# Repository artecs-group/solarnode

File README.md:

# Solar Node

This is a kikad project for a pcb of a IoT node that can meassure Solar Irradiation
and send it truogh a wifi conection to a cloud service.

The node ins based on an ESP32, which provides the microcontroller and the wifi
radio. The pcb adds a power supply system and a solar irradiance meassurement
circuit.

The power supply system is composed of a Lipo battery, a battery charger, a 6W
solar pannel and a set of regulators: one for the esp, and two for external
devices that can be swithced on or off from the ESP firmware.

The solar irradiance meassurement circuit is composed of a transimpedance
amplifier and a small mono-chrystalline fotovoltaic cell, that is kept in short
circuit by the transimpedance amplifier, which transforms the current generated
by the cell into a voltage that can be read using one of the ADC channels of the
ESP32. Bellow you can see an image of a complete node build from this pcb.

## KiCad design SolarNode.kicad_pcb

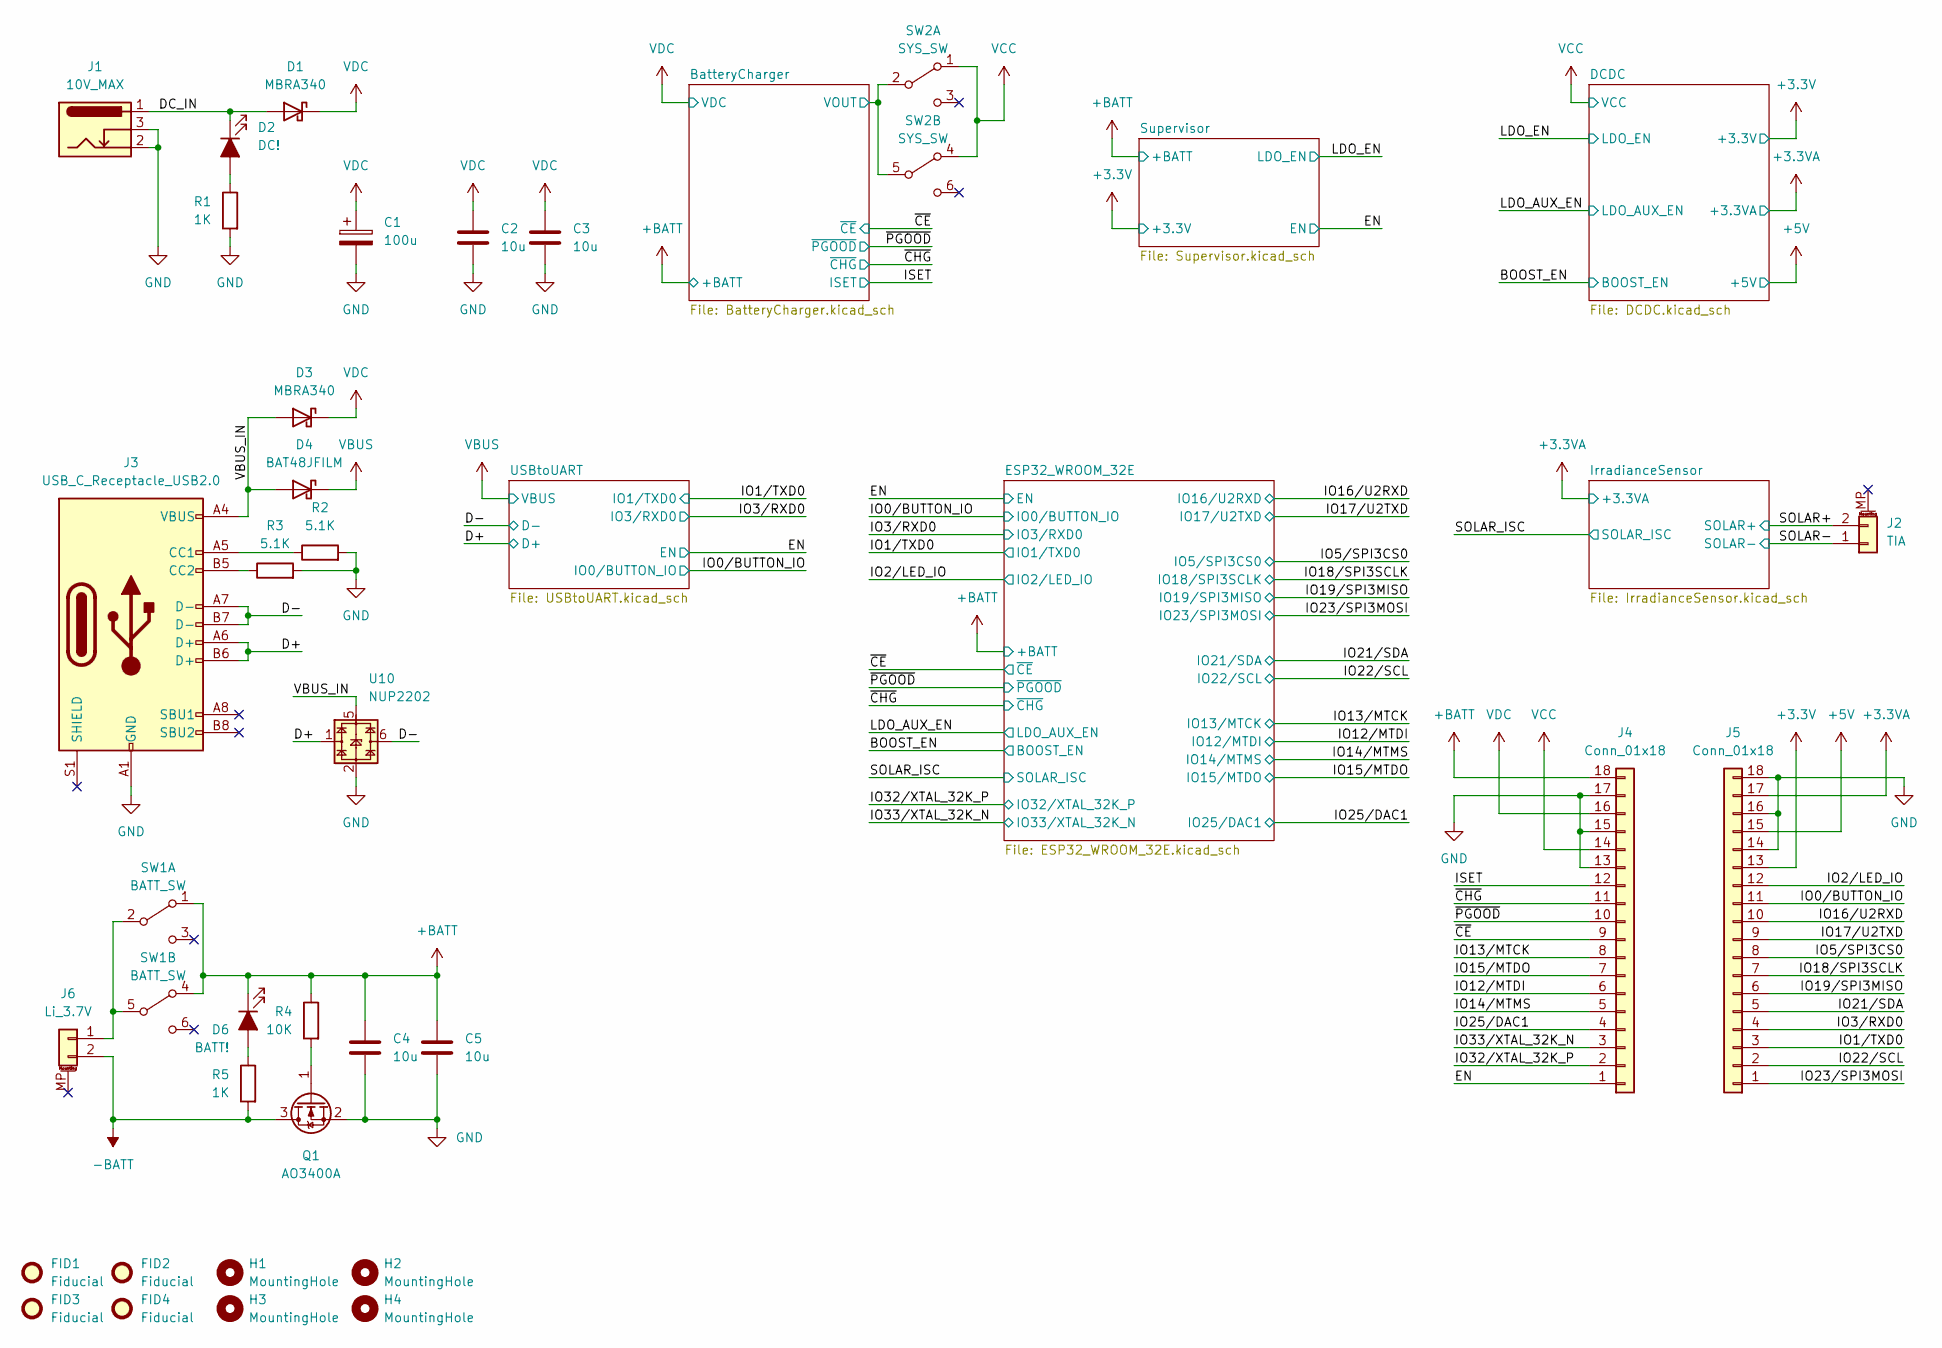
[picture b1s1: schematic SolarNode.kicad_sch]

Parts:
C1: 100u; CP_Radial_D6.3mm_P2.50mm; MPN 16YXF100MEFCT16.3X11
C2, C3, C4, C5: 10u; C_0603_1608Metric; MPN CC0603MRX5R7BB106
D1, D3: MBRA340; D_SMA; MPN MBRA340
D2: DC!; LED_0603_1608Metric; MPN 150060SS75000
D4: BAT48JFILM; D_SOD-323; MPN BAT48JFILM
D6: BATT!; LED_0603_1608Metric; MPN 150060SS75000
FID1, FID2, FID3, FID4: Fiducial; Fiducial_1mm_Mask3mm
H1, H2, H3, H4: MountingHole; MountingHole_2.2mm_M2
J1: 10V_MAX; BarrelJack_CLIFF_FC681465S_SMT_Horizontal; MPN FC681465S
J2: TIA; JST_PH_S2B-PH-SM4-TB_1x02-1MP_P2.00mm_Horizontal; MPN S2B-PH-SM4-TB(LF)(SN)
J3: USB_C_Receptacle_USB2.0; GCT_USB4110-GF-A_REVB; MPN USB4110-GF-A
J4, J5: Conn_01x18; PinHeader_1x18_P2.54mm_Vertical; MPN PH1-18-UA
J6: Li_3.7V; JST_PH_S2B-PH-SM4-TB_1x02-1MP_P2.00mm_Horizontal; MPN S2B-PH-SM4-TB(LF)(SN)
Q1: AO3400A; SOT-23; MPN AO3400A
R1, R5: 1K; R_0603_1608Metric_0.65; MPN RC0603FR-071KL
R2, R3: 5.1K; R_0603_1608Metric_0.65; MPN RC0603FR-075K1L
R4: 10K; R_0603_1608Metric_0.65; MPN RC0603FR-0710KL
SW1: BATT_SW; SW_DPDT_CK_JS202011JCQN; MPN JS202011JCQN
SW2: SYS_SW; SW_DPDT_CK_JS202011JCQN; MPN JS202011JCQN
U10: NUP2202; SOT-363_SC-70-6; MPN NUP2202W1T2G

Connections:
+3.3VA: J5.17; also elsewhere on the board
+3V3: J5.13; also elsewhere on the board
+5V: J5.15; also elsewhere on the board
+BATT: C4.1, C5.1, D6.1 (K), J4.18, R4.1, SW1.1 (A), SW1.4 (A); also elsewhere on the board
-BATT: J6.2, Q1.3 (D), R5.2
/BatteryCharger/VOUT: SW2.2 (B), SW2.5 (B); also elsewhere on the board
/D+: J3.A6 (D+), J3.B6 (D+), U10.1; also elsewhere on the board
/D-: J3.A7 (D-), J3.B7 (D-), U10.6; also elsewhere on the board
/DC_IN: D1.2 (A), D2.1 (K), J1.1
/EN: J4.1; also elsewhere on the board
/IO0/BUTTON_IO: J5.11; also elsewhere on the board
/IO1/TXD0: J5.3; also elsewhere on the board
/IO2/LED_IO: J5.12; also elsewhere on the board
/IO3/RXD0: J5.4; also elsewhere on the board
/IO5/SPI3CS0: J5.8; also elsewhere on the board
/IO12/MTDI: J4.6; also elsewhere on the board
/IO13/MTCK: J4.8; also elsewhere on the board
/IO14/MTMS: J4.5; also elsewhere on the board
/IO15/MTDO: J4.7; also elsewhere on the board
/IO16/U2RXD: J5.10; also elsewhere on the board
/IO17/U2TXD: J5.9; also elsewhere on the board
/IO18/SPI3SCLK: J5.7; also elsewhere on the board
/IO19/SPI3MISO: J5.6; also elsewhere on the board
/IO21/SDA: J5.5; also elsewhere on the board
/IO22/SCL: J5.2; also elsewhere on the board
/IO23/SPI3MOSI: J5.1; also elsewhere on the board
/IO25/DAC1: J4.4; also elsewhere on the board
/IO32/XTAL_32K_P: J4.2; also elsewhere on the board
/IO33/XTAL_32K_N: J4.3; also elsewhere on the board
/ISET: J4.12; also elsewhere on the board
/SOLAR+: J2.2; also elsewhere on the board
/SOLAR-: J2.1; also elsewhere on the board
/VBUS_IN: D3.2 (A), D4.2 (A), J3.A4 (VBUS), J3.A9 (VBUS), J3.B4 (VBUS), J3.B9 (VBUS), U10.5
/~CE: J4.9; also elsewhere on the board
/~CHG: J4.11; also elsewhere on the board
/~PGOOD: J4.10; also elsewhere on the board
GND: C1.2, C2.2, C3.2, C4.2, C5.2, J1.2, J1.3, J3.A1 (GND), J3.A12 (GND), J3.B1 (GND), J3.B12 (GND), J4.13, J4.15, J4.17, J5.14, J5.16, J5.18, Q1.2 (S), R1.2, R2.2, R3.2, U10.2; also elsewhere on the board
unnamed: D2.2 (A), R1.1
unnamed: D6.2 (A), R5.1
unnamed: J3.A5 (CC1), R2.1
unnamed: J3.B5 (CC2), R3.1
unnamed: J6.1, SW1.2 (B), SW1.5 (B)
unnamed: Q1.1 (G), R4.2
VBUS: D4.1 (K); also elsewhere on the board
VCC: J4.14, SW2.1 (A), SW2.4 (A); also elsewhere on the board
VDC: C1.1, C2.1, C3.1, D1.1 (K), D3.1 (K), J4.16; also elsewhere on the board

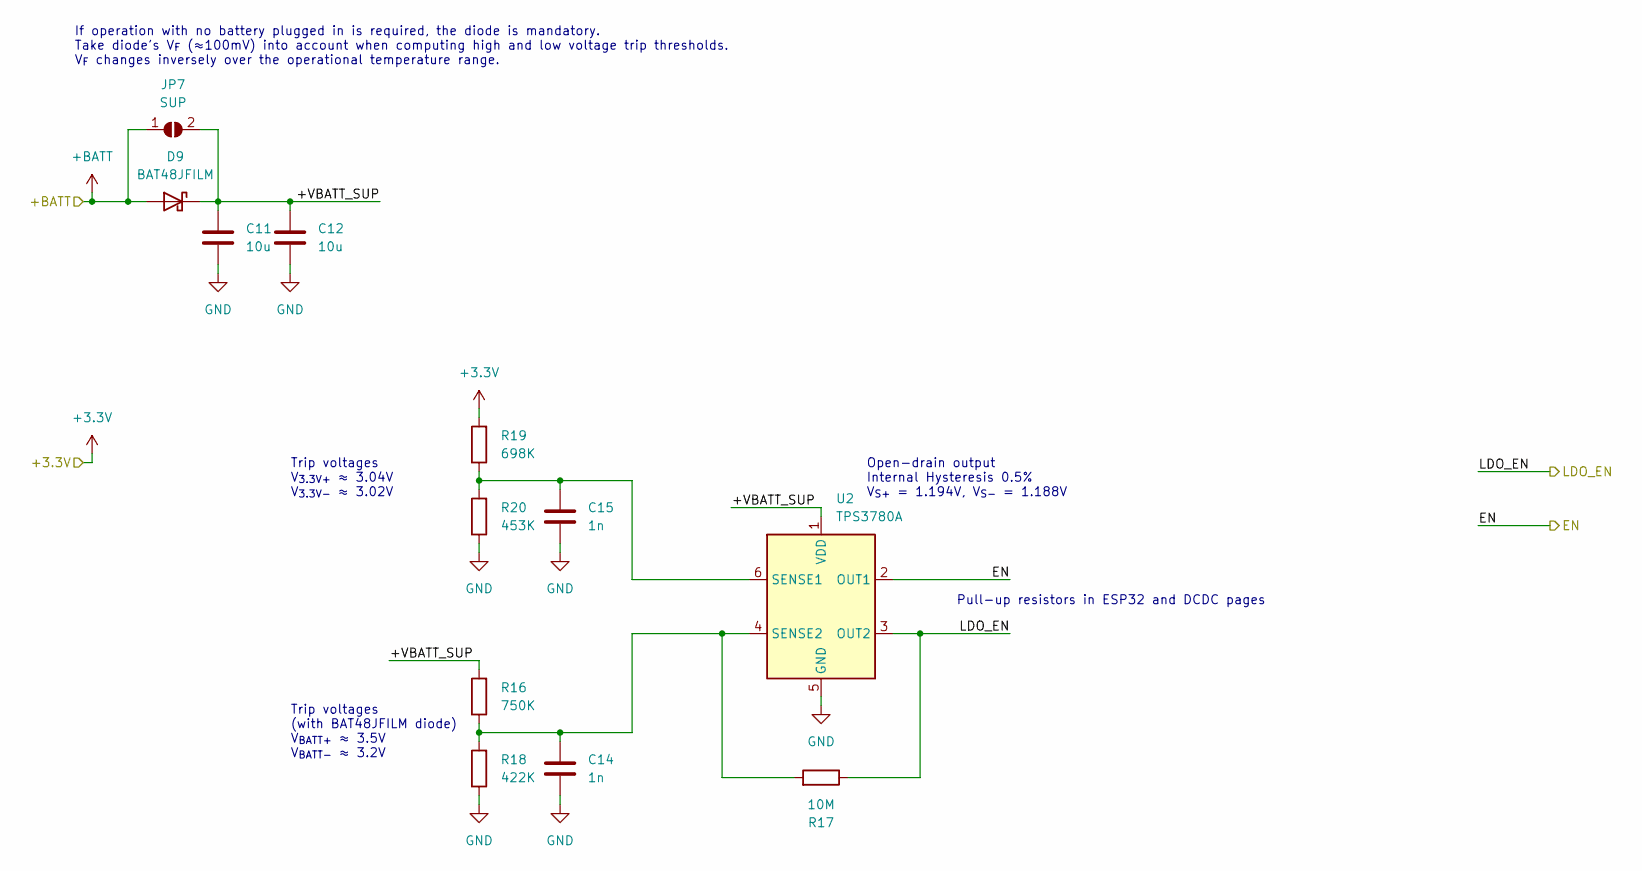
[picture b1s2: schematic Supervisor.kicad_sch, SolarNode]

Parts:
C11, C12: 10u; C_0603_1608Metric; MPN CC0603MRX5R7BB106
C14, C15: 1n; C_0603_1608Metric; MPN CC0603KRX7R9BB102
D9: BAT48JFILM; D_SOD-323; MPN BAT48JFILM
JP7: SUP; SolderJumper-2_P1.3mm_Open_RoundedPad1.0x1.5mm
R16: 750K; R_0603_1608Metric_0.65; MPN RC0603FR-07750KL
R17: 10M; R_0603_1608Metric_0.65; MPN RC0603FR-0710ML
R18: 422K; R_0603_1608Metric_0.65; MPN RC0603FR-07422KL
R19: 698K; R_0603_1608Metric_0.65; MPN RC0603FR-07698KL
R20: 453K; R_0603_1608Metric_0.65; MPN RC0603FR-07453KL
U2: TPS3780A; SOT-23-6; MPN TPS3780ADBVT

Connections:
+3V3: R19.2; also elsewhere on the board
+BATT: D9.2 (A), JP7.1 (A); also elsewhere on the board
/EN: U2.2 (OUT1); also elsewhere on the board
/LDO_EN: R17.1, U2.3 (OUT2); also elsewhere on the board
/Supervisor/+VBATT_SUP: C11.1, C12.1, D9.1 (K), JP7.2 (B), R16.2, U2.1 (VDD)
GND: C11.2, C12.2, C14.2, C15.2, R18.1, R20.1, U2.5 (GND); also elsewhere on the board
unnamed: C14.1, R16.1, R17.2, R18.2, U2.4 (SENSE2)
unnamed: C15.1, R19.1, R20.2, U2.6 (SENSE1)

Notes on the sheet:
Trip voltages V_{3.3V+} ≈ 3.04V V_{3.3V-} ≈ 3.02V
Pull-up resistors in ESP32 and DCDC pages
Trip voltages (with BAT48JFILM diode) V_{BATT+} ≈ 3.5V V_{BATT-} ≈ 3.2V
If operation with no battery plugged in is required, the diode is mandatory. Take diode's V_{F} (≈100mV) into account when computing high and low voltage trip thresholds. V_{F} changes inversely over the operational temperature range.
Open-drain output Internal Hysteresis 0.5% V_{S+} = 1.194V, V_{S-} = 1.188V

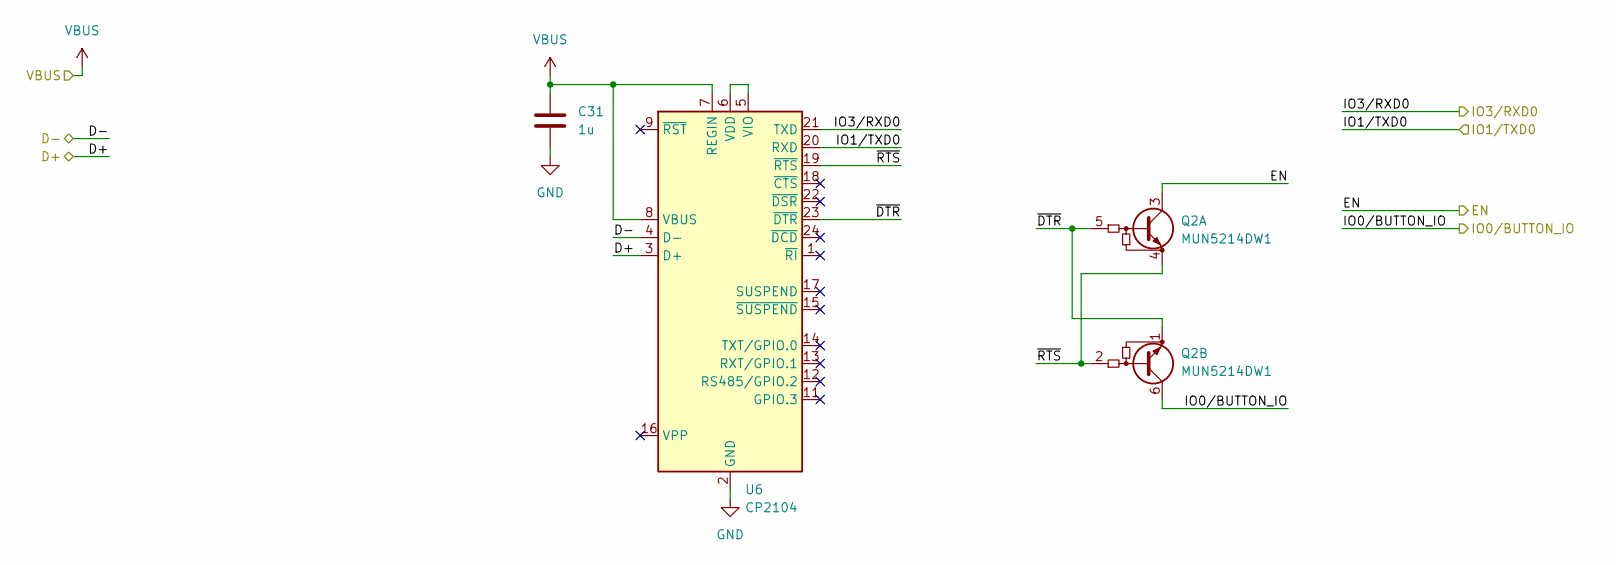
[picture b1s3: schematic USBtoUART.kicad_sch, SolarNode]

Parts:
C31: 1u; C_0603_1608Metric; MPN CC0603KRX7R8BB105
Q2: MUN5214DW1; SOT-363_SC-70-6; MPN MUN5214DW1T1G
U6: CP2104; QFN-24-1EP_4x4mm_P0.5mm_EP2.6x2.6mm; MPN CP2104-F03-GM

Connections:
/D+: U6.3 (D+); also elsewhere on the board
/D-: U6.4 (D-); also elsewhere on the board
/EN: Q2.3 (C1); also elsewhere on the board
/IO0/BUTTON_IO: Q2.6 (C2); also elsewhere on the board
/IO1/TXD0: U6.20 (RXD); also elsewhere on the board
/IO3/RXD0: U6.21 (TXD); also elsewhere on the board
/USBtoUART/~DTR: Q2.1 (E2), Q2.5 (B1), U6.23 (~DTR)
/USBtoUART/~RTS: Q2.2 (B2), Q2.4 (E1), U6.19 (~RTS)
GND: C31.2, U6.2 (GND), U6.25 (GND); also elsewhere on the board
unnamed: U6.5 (VIO), U6.6 (VDD)
VBUS: C31.1, U6.7 (REGIN), U6.8 (VBUS); also elsewhere on the board

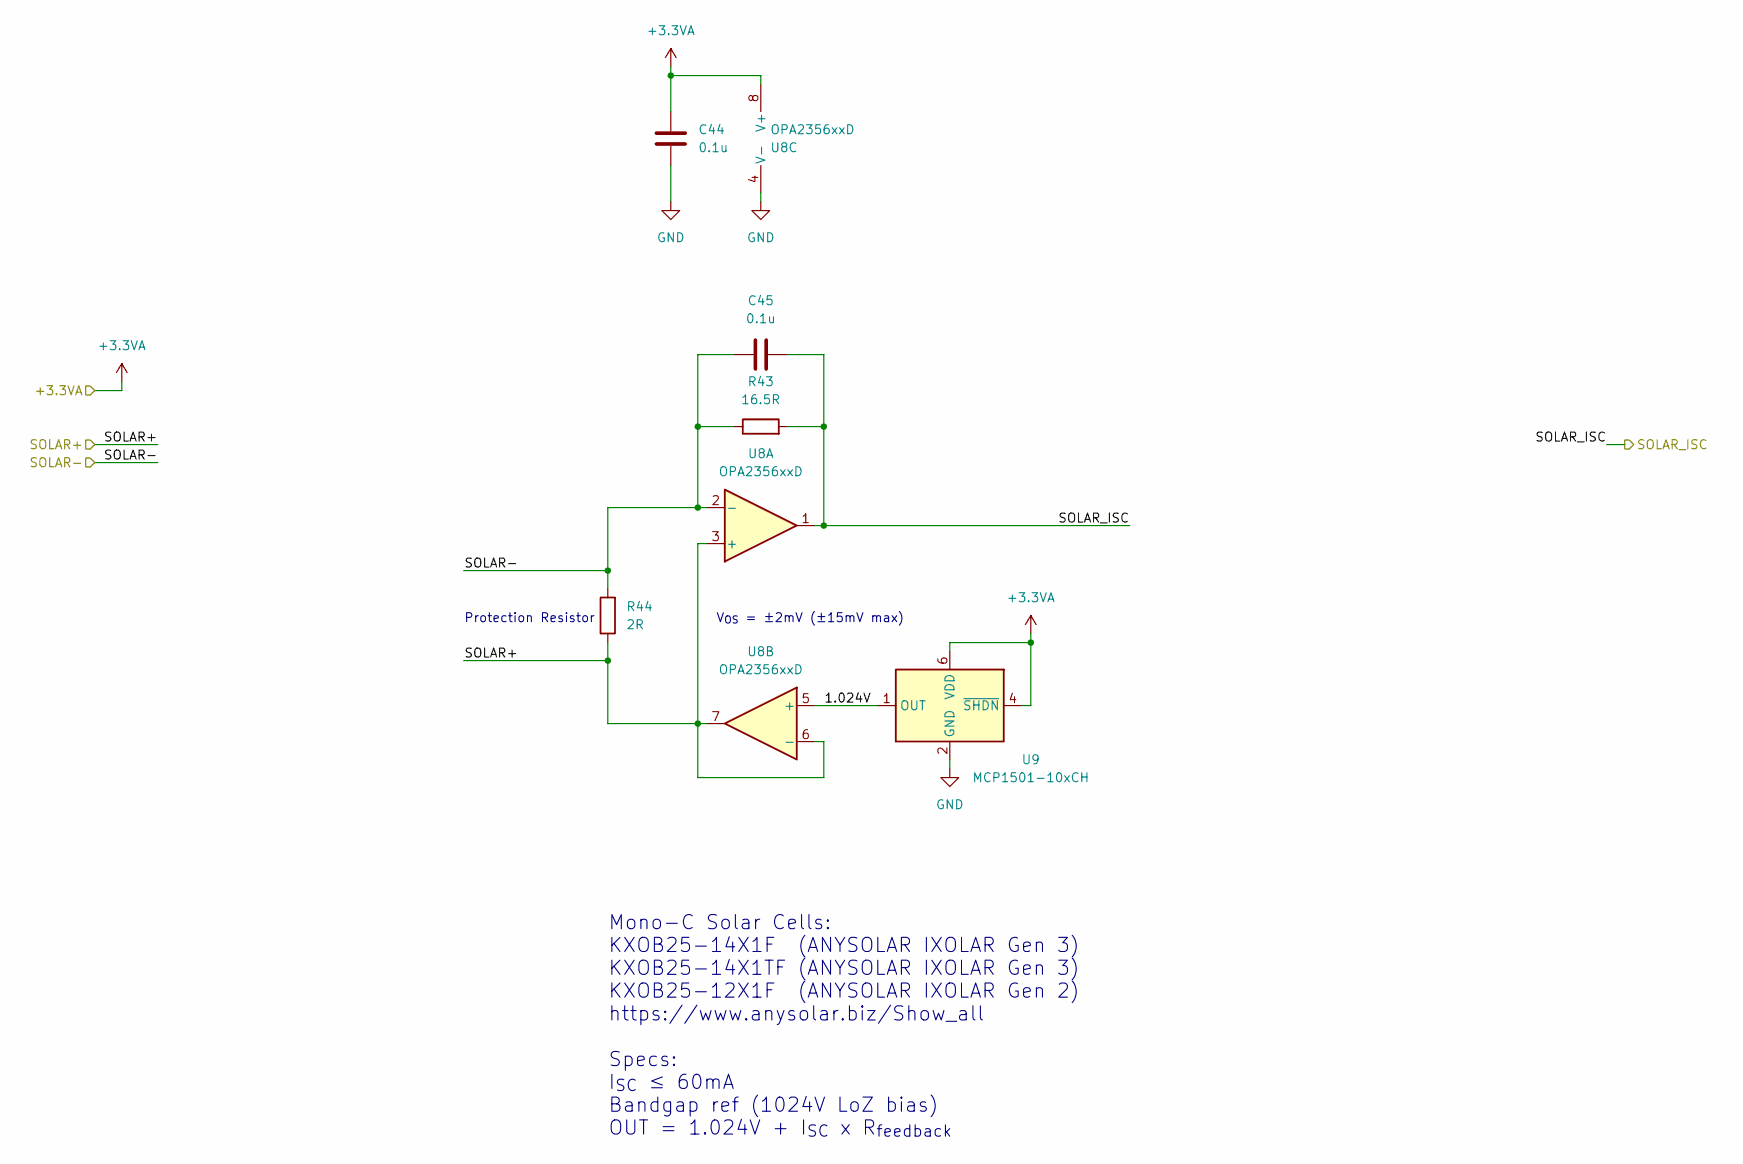
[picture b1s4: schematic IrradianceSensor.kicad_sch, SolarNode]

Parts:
C44, C45: 0.1u; C_0603_1608Metric; MPN CC0603KRX7R9BB104
R43: 16.5R; R_0603_1608Metric_0.65; MPN RC0603FR-0716R5L
R44: 2R; R_0603_1608Metric_0.65; MPN RC0603FR-072RL
U8: OPA2356xxD; MSOP-8_3x3mm_P0.65mm; MPN OPA2356AIDGKR
U9: MCP1501-10xCH; SOT-23-6; MPN MCP1501T-10E/CHY

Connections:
+3.3VA: C44.1, U8.8 (V+), U9.4 (~SHDN), U9.6 (VDD); also elsewhere on the board
/IrradianceSensor/1.024V: U8.5 (+), U9.1 (OUT)
/SOLAR+: R44.1, U8.3 (+), U8.6 (-), U8.7; also elsewhere on the board
/SOLAR-: C45.1, R43.1, R44.2, U8.2 (-); also elsewhere on the board
/SOLAR_ISC: C45.2, R43.2, U8.1; also elsewhere on the board
GND: C44.2, U8.4 (V-), U9.2 (GND), U9.3 (GND), U9.5 (GND); also elsewhere on the board

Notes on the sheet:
Mono-C Solar Cells: KXOB25-14X1F (ANYSOLAR IXOLAR Gen 3) KXOB25-14X1TF (ANYSOLAR IXOLAR Gen 3) KXOB25-12X1F (ANYSOLAR IXOLAR Gen 2) https://www.anysolar.biz/Show_all Specs: I_{SC} ≤ 60mA Bandgap ref (1024V LoZ bias) OUT = 1.024V + I_{SC} x R_{feedback}
V_{OS} = ±2mV (±15mV max)
Protection Resistor

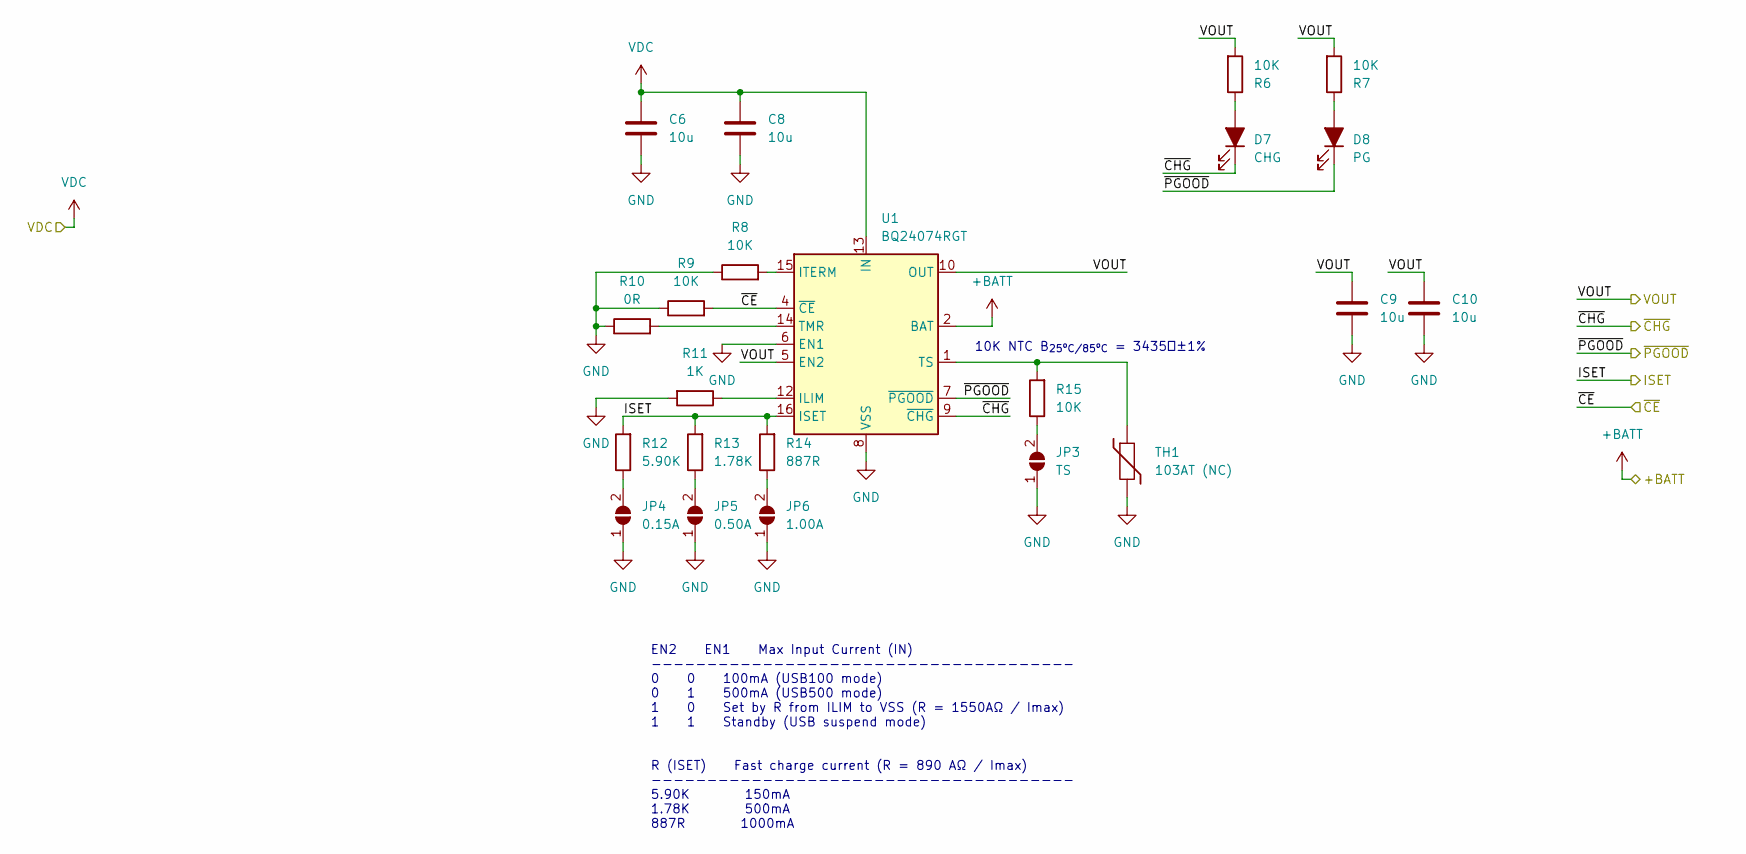
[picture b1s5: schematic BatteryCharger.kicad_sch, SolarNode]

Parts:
C6, C8, C9, C10: 10u; C_0603_1608Metric; MPN CC0603MRX5R7BB106
D7: CHG; LED_0603_1608Metric; MPN 150060SS75000
D8: PG; LED_0603_1608Metric; MPN 150060VS75000
JP3: TS; SolderJumper-2_P1.3mm_Open_RoundedPad1.0x1.5mm
JP4: 0.15A; SolderJumper-2_P1.3mm_Open_RoundedPad1.0x1.5mm
JP5: 0.50A; SolderJumper-2_P1.3mm_Open_RoundedPad1.0x1.5mm
JP6: 1.00A; SolderJumper-2_P1.3mm_Open_RoundedPad1.0x1.5mm
R6, R7, R8, R9, R15: 10K; R_0603_1608Metric_0.65; MPN RC0603FR-0710KL
R10: 0R; R_0603_1608Metric_0.65; MPN RC0603FR-070RL
R11: 1K; R_0603_1608Metric_0.65; MPN RC0603FR-071KL
R12: 5.90K; R_0603_1608Metric_0.65; MPN RC0603FR-075K9L
R13: 1.78K; R_0603_1608Metric_0.65; MPN RC0603FR-071K78L
R14: 887R; R_0603_1608Metric_0.65; MPN RC0603FR-07887RL
TH1: 103AT (NC); C_Disc_D5.0mm_W2.5mm_P2.50mm; MPN 103AT-2
U1: BQ24074RGT; VQFN-16-1EP_3x3mm_P0.5mm_EP1.6x1.6mm_ThermalVias; MPN BQ24074RGT

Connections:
+BATT: U1.2 (BAT), U1.3 (BAT); also elsewhere on the board
/BatteryCharger/VOUT: C9.1, C10.1, R6.2, R7.2, U1.5 (EN2), U1.10 (OUT), U1.11 (OUT); also elsewhere on the board
/ISET: R12.2, R13.2, R14.2, U1.16 (ISET); also elsewhere on the board
/~CE: R9.2, U1.4 (~CE); also elsewhere on the board
/~CHG: D7.1 (K), U1.9 (~CHG); also elsewhere on the board
/~PGOOD: D8.1 (K), U1.7 (~PGOOD); also elsewhere on the board
GND: C6.2, C8.2, C9.2, C10.2, JP3.1 (A), JP4.1 (A), JP5.1 (A), JP6.1 (A), R8.1, R9.1, R10.1, R11.2, TH1.2, U1.6 (EN1), U1.8 (VSS), U1.17 (VSS); also elsewhere on the board
unnamed: D7.2 (A), R6.1
unnamed: D8.2 (A), R7.1
unnamed: JP3.2 (B), R15.1
unnamed: JP4.2 (B), R12.1
unnamed: JP5.2 (B), R13.1
unnamed: JP6.2 (B), R14.1
unnamed: R8.2, U1.15 (ITERM)
unnamed: R10.2, U1.14 (TMR)
unnamed: R11.1, U1.12 (ILIM)
unnamed: R15.2, TH1.1, U1.1 (TS)
VDC: C6.1, C8.1, U1.13 (IN); also elsewhere on the board

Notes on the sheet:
EN2 EN1 Max Input Current (IN) -------------------------------------- 0 0 100mA (USB100 mode) 0 1 500mA (USB500 mode) 1 0 Set by R from ILIM to VSS (R = 1550AΩ / Imax) 1 1 Standby (USB suspend mode) R (ISET) Fast charge current (R = 890 AΩ / Imax) -------------------------------------- 5.90K 150mA 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
10K NTC B_{25ºC/85ºC} = 3435Ｋ±1%

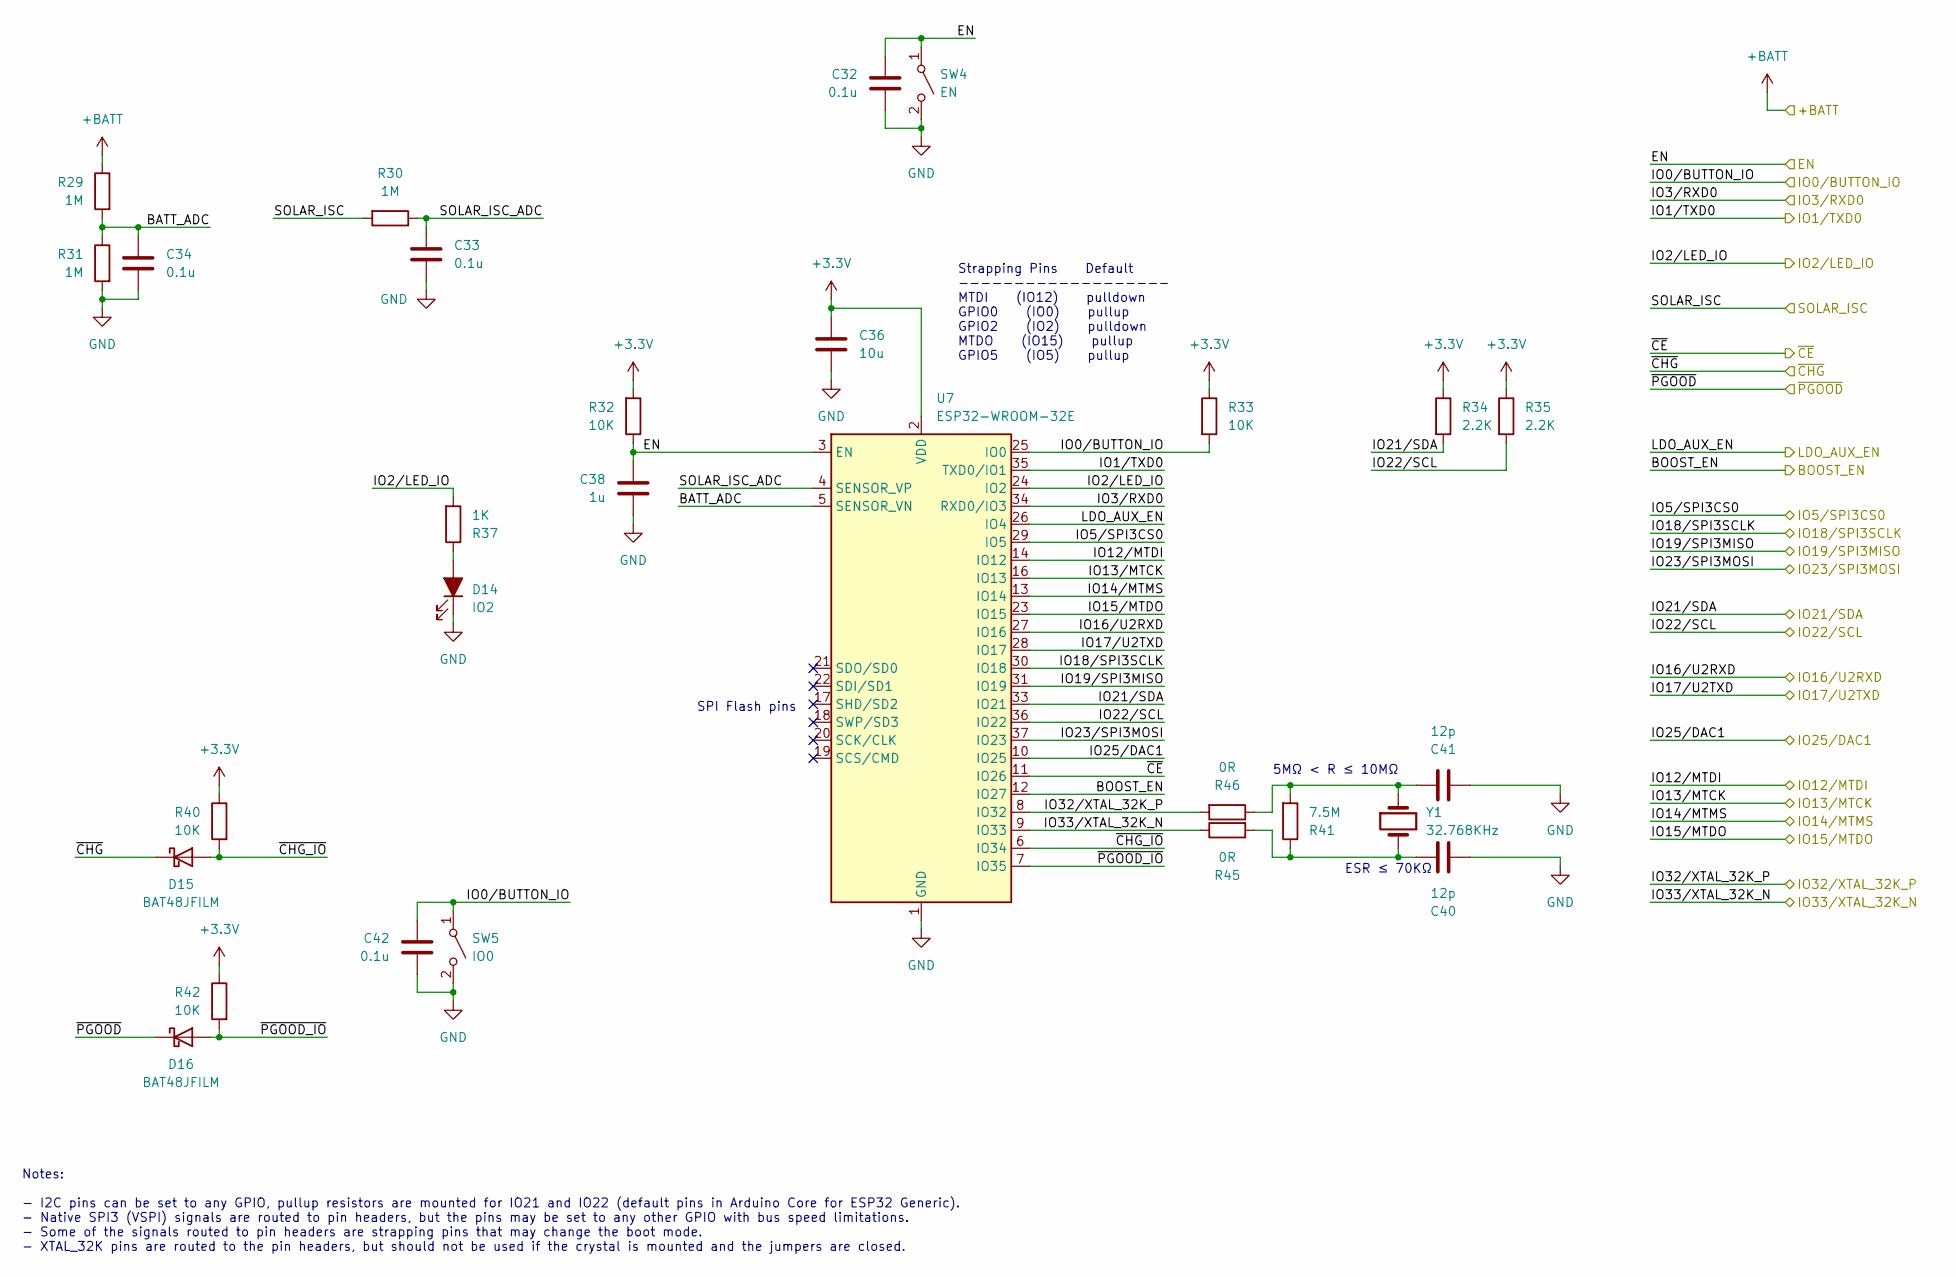
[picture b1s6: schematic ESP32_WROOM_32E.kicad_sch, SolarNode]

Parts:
C32, C33, C34, C42: 0.1u; C_0603_1608Metric; MPN CC0603KRX7R9BB104
C36: 10u; C_0603_1608Metric; MPN CC0603MRX5R7BB106
C38: 1u; C_0603_1608Metric; MPN CC0603KRX7R8BB105
C40, C41: 12p; C_0603_1608Metric; MPN CC0603KRNPO9BN120
D14: IO2; LED_0603_1608Metric; MPN 150060VS75000
D15, D16: BAT48JFILM; D_SOD-323; MPN BAT48JFILM
R29, R30, R31: 1M; R_0603_1608Metric_0.65; MPN RC0603FR-071ML
R32, R33, R40, R42: 10K; R_0603_1608Metric_0.65; MPN RC0603FR-0710KL
R34, R35: 2.2K; R_0603_1608Metric_0.65; MPN RC0603FR-072K2L
R37: 1K; R_0603_1608Metric_0.65; MPN RC0603FR-071KL
R41: 7.5M; R_0603_1608Metric_0.65; MPN RC0603FR-077M5L
R45, R46: 0R; R_0603_1608Metric_0.65; MPN RC0603FR-070RL
SW4: EN; SW_SPST_B3U-1000P; MPN B3U-1000P
SW5: IO0; SW_SPST_B3U-1000P; MPN B3U-1000P
U7: ESP32-WROOM-32E; ESP32-WROOM-32; MPN ESP32-WROOM-32E (4MB)
Y1: 32.768KHz; Crystal_SMD_3215-2Pin_3.2x1.5mm; MPN FC-135 32.7680KA-K0

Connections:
+3V3: C36.1, R32.2, R33.1, R34.1, R35.1, R40.1, R42.1, U7.2 (VDD); also elsewhere on the board
+BATT: R29.1; also elsewhere on the board
/BOOST_EN: U7.12 (IO27); also elsewhere on the board
/EN: C32.1, C38.2, R32.1, SW4.1 (A), U7.3 (EN); also elsewhere on the board
/ESP32_WROOM_32E/BATT_ADC: C34.1, R29.2, R31.1, U7.5 (SENSOR_VN)
/ESP32_WROOM_32E/SOLAR_ISC_ADC: C33.1, R30.1, U7.4 (SENSOR_VP)
/ESP32_WROOM_32E/~CHG_IO: D15.2 (A), R40.2, U7.6 (IO34)
/ESP32_WROOM_32E/~PGOOD_IO: D16.2 (A), R42.2, U7.7 (IO35)
/IO0/BUTTON_IO: C42.1, R33.2, SW5.1 (A), U7.25 (IO0); also elsewhere on the board
/IO1/TXD0: U7.35 (TXD0/IO1); also elsewhere on the board
/IO2/LED_IO: R37.2, U7.24 (IO2); also elsewhere on the board
/IO3/RXD0: U7.34 (RXD0/IO3); also elsewhere on the board
/IO5/SPI3CS0: U7.29 (IO5); also elsewhere on the board
/IO12/MTDI: U7.14 (IO12); also elsewhere on the board
/IO13/MTCK: U7.16 (IO13); also elsewhere on the board
/IO14/MTMS: U7.13 (IO14); also elsewhere on the board
/IO15/MTDO: U7.23 (IO15); also elsewhere on the board
/IO16/U2RXD: U7.27 (IO16); also elsewhere on the board
/IO17/U2TXD: U7.28 (IO17); also elsewhere on the board
/IO18/SPI3SCLK: U7.30 (IO18); also elsewhere on the board
/IO19/SPI3MISO: U7.31 (IO19); also elsewhere on the board
/IO21/SDA: R34.2, U7.33 (IO21); also elsewhere on the board
/IO22/SCL: R35.2, U7.36 (IO22); also elsewhere on the board
/IO23/SPI3MOSI: U7.37 (IO23); also elsewhere on the board
/IO25/DAC1: U7.10 (IO25); also elsewhere on the board
/IO32/XTAL_32K_P: R46.2, U7.8 (IO32); also elsewhere on the board
/IO33/XTAL_32K_N: R45.1, U7.9 (IO33); also elsewhere on the board
/LDO_AUX_EN: U7.26 (IO4); also elsewhere on the board
/SOLAR_ISC: R30.2; also elsewhere on the board
/~CE: U7.11 (IO26); also elsewhere on the board
/~CHG: D15.1 (K); also elsewhere on the board
/~PGOOD: D16.1 (K); also elsewhere on the board
GND: C32.2, C33.2, C34.2, C36.2, C38.1, C40.2, C41.2, C42.2, D14.1 (K), R31.2, SW4.2 (B), SW5.2 (B), U7.1 (GND), U7.15 (GND), U7.38 (GND), U7.39 (GND); also elsewhere on the board
unnamed: C40.1, R41.1, R45.2, Y1.2
unnamed: C41.1, R41.2, R46.1, Y1.1
unnamed: D14.2 (A), R37.1

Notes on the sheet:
Strapping Pins Default ------------------- MTDI (IO12) pulldown GPIO0 (IO0) pullup GPIO2 (IO2) pulldown MTDO (IO15) pullup GPIO5 (IO5) pullup
SPI Flash pins
Notes: - I2C pins can be set to any GPIO, pullup resistors are mounted for IO21 and IO22 (default pins in Arduino Core for ESP32 Generic). - Native SPI3 (VSPI) signals are routed to pin headers, but the pins may be set to any other GPIO with bus speed limitations. - Some of the signals routed to pi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
5MΩ < R ≤ 10MΩ
ESR ≤ 70KΩ

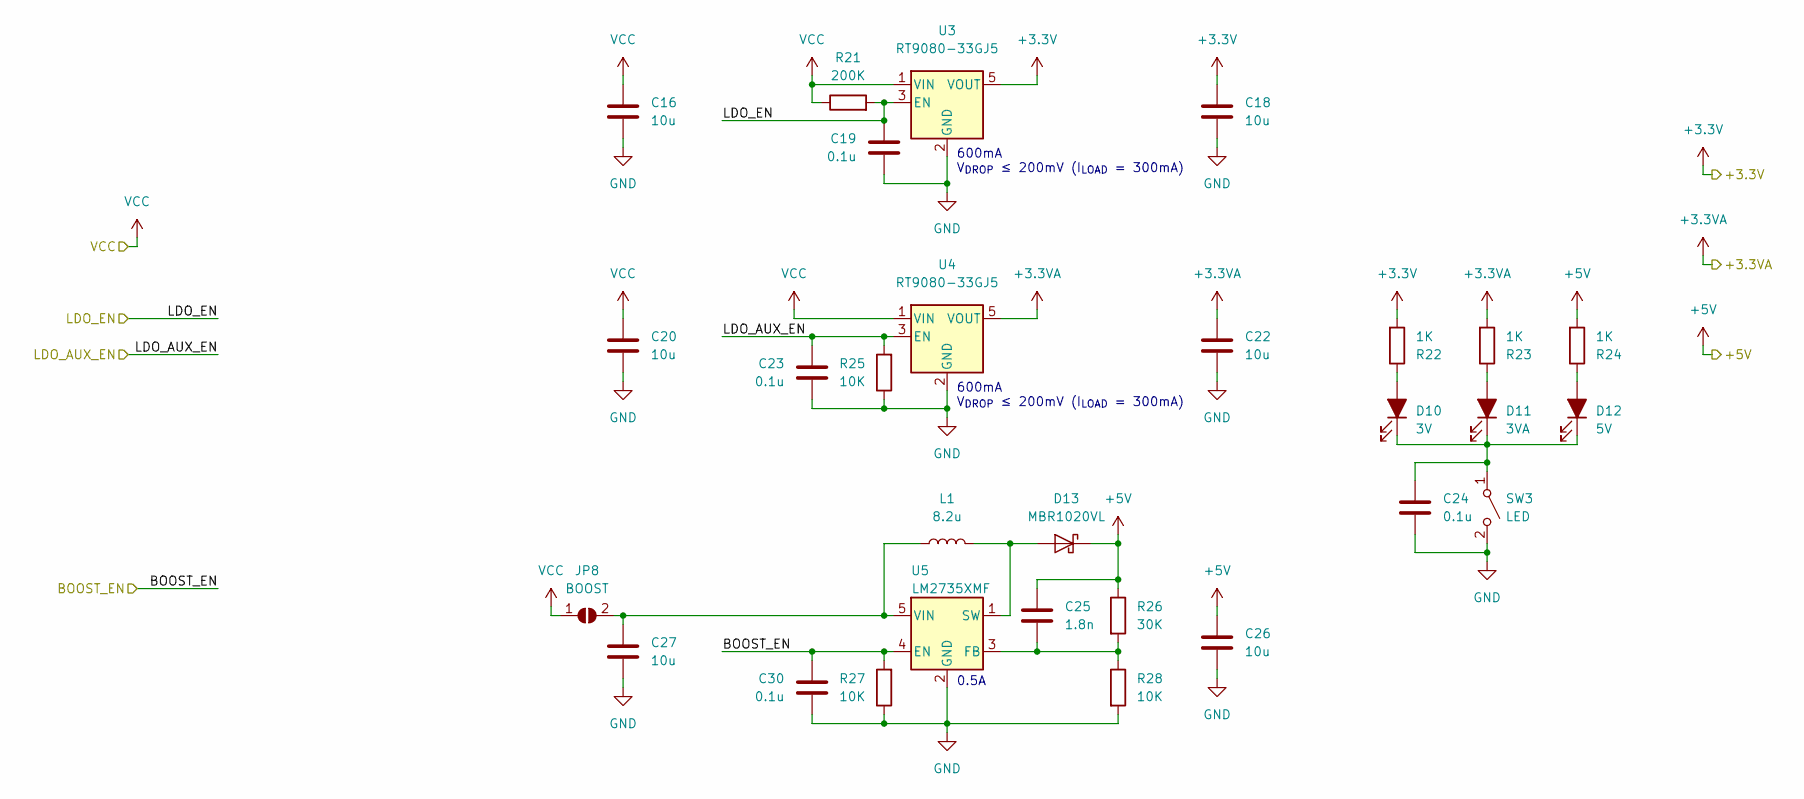
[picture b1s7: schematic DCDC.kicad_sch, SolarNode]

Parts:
C16, C18, C20, C22, C26, C27: 10u; C_0603_1608Metric; MPN CC0603MRX5R7BB106
C19, C23, C24, C30: 0.1u; C_0603_1608Metric; MPN CC0603KRX7R9BB104
C25: 1.8n; C_0603_1608Metric; MPN CC0603KRX7R9BB182
D10: 3V; LED_0603_1608Metric; MPN 150060VS75000
D11: 3VA; LED_0603_1608Metric; MPN 150060VS75000
D12: 5V; LED_0603_1608Metric; MPN 150060VS75000
D13: MBR1020VL; D_SOD-123F; MPN MBR1020VL
JP8: BOOST; SolderJumper-2_P1.3mm_Open_RoundedPad1.0x1.5mm
L1: 8.2u; L_Vishay_IFSC-1515AH_4x4x1.8mm; MPN IFSC1515AHER8R2M01
R21: 200K; R_0603_1608Metric_0.65; MPN RC0603FR-07200KL
R22, R23, R24: 1K; R_0603_1608Metric_0.65; MPN RC0603FR-071KL
R25, R27, R28: 10K; R_0603_1608Metric_0.65; MPN RC0603FR-0710KL
R26: 30K; R_0603_1608Metric_0.65; MPN RC0603FR-0730KL
SW3: LED; SW_SPST_B3U-1000P; MPN B3U-1000P
U3, U4: RT9080-33GJ5; SOT-23-5; MPN RT9080-33GJ5
U5: LM2735XMF; SOT-23-5; MPN LM2735XMF/NOPB

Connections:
+3.3VA: C22.1, R23.2, U4.5 (VOUT); also elsewhere on the board
+3V3: C18.1, R22.2, U3.5 (VOUT); also elsewhere on the board
+5V: C25.1, C26.1, D13.1 (K), R24.2, R26.1; also elsewhere on the board
/BOOST_EN: C30.1, R27.2, U5.4 (EN); also elsewhere on the board
/LDO_AUX_EN: C23.1, R25.2, U4.3 (EN); also elsewhere on the board
/LDO_EN: C19.1, R21.2, U3.3 (EN); also elsewhere on the board
GND: C16.2, C18.2, C19.2, C20.2, C22.2, C23.2, C24.2, C26.2, C27.2, C30.2, R25.1, R27.1, R28.2, SW3.2 (B), U3.2 (GND), U4.2 (GND), U5.2 (GND); also elsewhere on the board
unnamed: C24.1, D10.1 (K), D11.1 (K), D12.1 (K), SW3.1 (A)
unnamed: C25.2, R26.2, R28.1, U5.3 (FB)
unnamed: C27.1, JP8.2 (B), L1.1, U5.5 (VIN)
unnamed: D10.2 (A), R22.1
unnamed: D11.2 (A), R23.1
unnamed: D12.2 (A), R24.1
unnamed: D13.2 (A), L1.2, U5.1 (SW)
VCC: C16.1, C20.1, JP8.1 (A), R21.1, U3.1 (VIN), U4.1 (VIN); also elsewhere on the board

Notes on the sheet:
0.5A
600mA V_{DROP} ≤ 200mV (I_{LOAD} = 300mA)
